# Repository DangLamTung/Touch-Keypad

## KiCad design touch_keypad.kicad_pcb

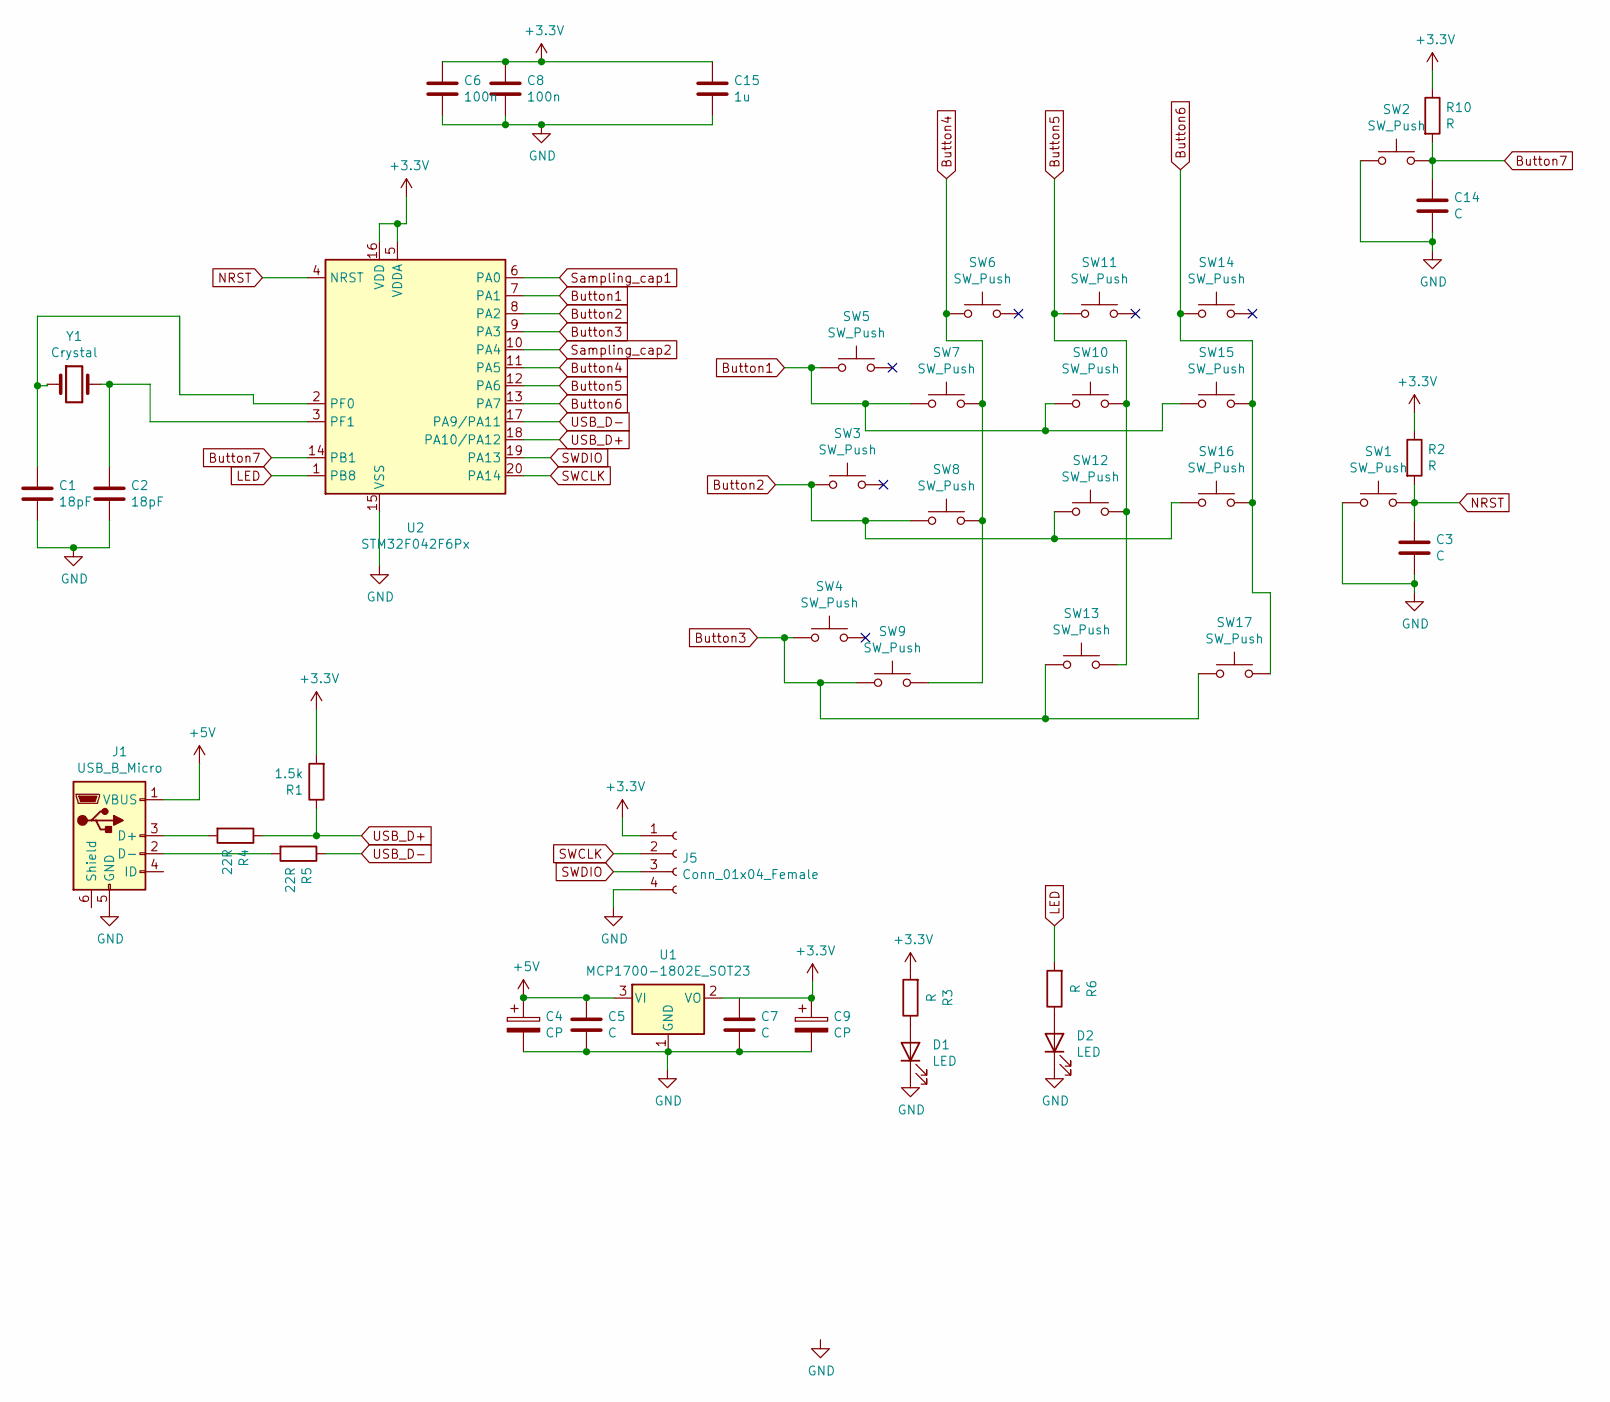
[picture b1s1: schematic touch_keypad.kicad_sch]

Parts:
C1, C2: 18pF; C_0402_1005Metric
C3, C5, C7, C14: C; C_0603_1608Metric_Pad1.05x0.95mm_HandSolder
C4, C9: CP; C_1206_3216Metric
C6, C8: 100n; C_0603_1608Metric_Pad1.05x0.95mm_HandSolder
C15: 1u; C_0603_1608Metric_Pad1.05x0.95mm_HandSolder
D1, D2: LED; LED_0603_1608Metric
J1: USB_B_Micro; USB_Micro-B_Molex-105017-0001
J5: Conn_01x04_Female; PinHeader_1x04_P2.54mm_Vertical
R1: 1.5k; R_0603_1608Metric
R2, R3, R6, R10: R; R_0603_1608Metric_Pad1.05x0.95mm_HandSolder
R4, R5: 22R; R_0603_1608Metric
SW1, SW2: SW_Push; SW_Push_1P1T_NO_6x6mm_H9.5mm
SW3, SW4, SW5, SW6, SW11, SW14: SW_Push; cap_button
SW7, SW8, SW9, SW10, SW12, SW13, SW15, SW16, SW17: SW_Push; TouchSlider-2_10x10mm
U1: MCP1700-1802E_SOT23; SOT-23
U2: STM32F042F6Px; TSSOP-20_4.4x6.5mm_P0.65mm
Y1: Crystal; Crystal_HC18-U_Vertical

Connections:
+3V3: C6.1, C8.1, C9.1, C15.1, J5.1, R1.2, R2.1, R3.2, R10.1, U1.2 (VO), U2.5 (VDDA), U2.16 (VDD)
+5V: C4.1, C5.1, J1.1 (VBUS), U1.3 (VI)
Button1: SW5.1, SW7.1, SW10.1, SW15.1, U2.7 (PA1)
Button2: SW3.1, SW8.1, SW12.1, SW16.1, U2.8 (PA2)
Button3: SW4.1, SW9.1, SW13.1, SW17.1, U2.9 (PA3)
Button4: SW6.1, SW7.2, SW8.2, SW9.2, U2.11 (PA5)
Button5: SW10.2, SW11.1, SW12.2, SW13.2, U2.12 (PA6)
Button6: SW14.1, SW15.2, SW16.2, SW17.2, U2.13 (PA7)
Button7: C14.1, R10.2, SW2.2, U2.14 (PB1)
GND: C1.2, C2.2, C3.2, C4.2, C5.2, C6.2, C7.2, C8.2, C9.2, C14.2, C15.2, D1.1 (K), D2.1 (K), J1.5 (GND), J5.4, SW1.1, SW2.1, U1.1 (GND), U2.15 (VSS)
LED: R6.2, U2.1 (PB8)
NRST: C3.1, R2.2, SW1.2, U2.4 (NRST)
unnamed: C1.1, U2.2 (PF0), Y1.1
unnamed: C2.1, U2.3 (PF1), Y1.2
unnamed: D1.2 (A), R3.1
unnamed: D2.2 (A), R6.1
unnamed: J1.2 (D-), R5.2
unnamed: J1.3 (D+), R4.2
SWCLK: J5.2, U2.20 (PA14)
SWDIO: J5.3, U2.19 (PA13)
Sampling_cap1: U2.6 (PA0)
Sampling_cap2: U2.10 (PA4)
USB_D+: R1.1, R4.1, U2.18 (PA10/PA12)
USB_D-: R5.1, U2.17 (PA9/PA11)

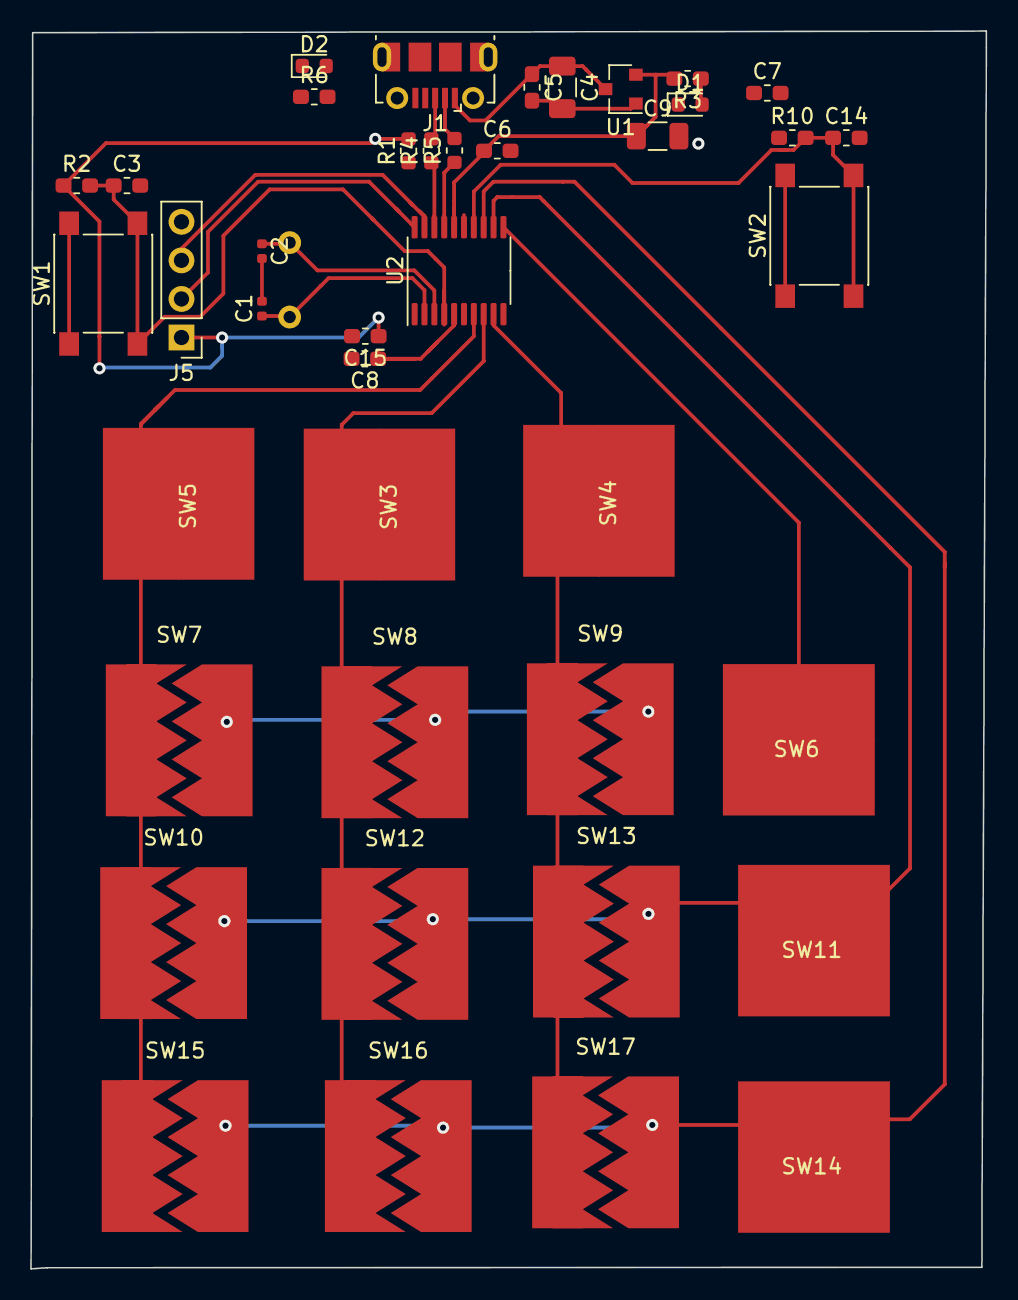
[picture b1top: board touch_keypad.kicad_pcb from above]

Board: 2 copper layers, 62.9 x 81.5 mm, 42 parts (1 on the bottom side), 22 nets.

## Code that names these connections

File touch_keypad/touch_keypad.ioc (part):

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Mcu.Name=STM32F042F6Px
Mcu.Package=TSSOP20
Mcu.UserName=STM32F042F6Px
PA0.Mode=G1_IO1-Channel
PA0.Signal=TSC_G1_IO1
PA1.Mode=G1_IO2-Channel
PA1.Signal=TSC_G1_IO2
PA11.Mode=Device
PA11.Signal=USB_DM
PA12.Mode=Device
PA12.Signal=USB_DP
PA13.Mode=Serial_Wire
PA13.Signal=SYS_SWDIO
PA14.Mode=Serial_Wire
PA14.Signal=SYS_SWCLK
PA2.Mode=G1_IO3-Channel
PA2.Signal=TSC_G1_IO3
PA3.Mode=G1_IO4-Sampling
PA3.Signal=TSC_G1_IO4
PA4.Mode=G2_IO1-Sampling
PA4.Signal=TSC_G2_IO1
PA5.Mode=G2_IO2-Channel
PA5.Signal=TSC_G2_IO2
PA6.Mode=G2_IO3-Channel
PA6.Signal=TSC_G2_IO3
PA7.Mode=G2_IO4-Channel
PA7.Signal=TSC_G2_IO4
PB8.Signal=GPIO_Output
PF0-OSC_IN.Mode=HSE-External-Oscillator
PF0-OSC_IN.Signal=RCC_OSC_IN
PF1-OSC_OUT.Mode=HSE-External-Oscillator
PF1-OSC_OUT.Signal=RCC_OSC_OUT
RCC.SYSCLKFreq_VALUE=48000000
RCC.SYSCLKSource=RCC_SYSCLKSOURCE_PLLCLK
board=custom

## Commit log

2020-09-09 add alot
2020-09-11 upgrade to kicad 6
2020-09-11 output
2020-09-14 add code
